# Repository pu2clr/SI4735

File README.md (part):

<meta name="google-site-verification" content="_wADvyP4vuP_aw0YTmu90mdAhz70vNwTF_pdAMMb0HY" />

# [PU2CLR SI4735 Library for Arduino](https://pu2clr.github.io/SI4735/)

[Se você estiver entendendo este texto, talvez queira ler este documento em Português](https://pu2clr.github.io/SI4735/extras/docbr/)

# Preface

|          |            |
|----------|------------|
|    | This document is aimed at the Arduino developers, radio experimenters, hobbyists and anyone interested in building a receiver based on the Si473X IC family from Silicon Labs. This project is about an Arduino library for the SI473X BROADCAST AM, SSB and FM/RDS RADIO RECEIVERS. Frequency ranges of AM and SSB modes are 150kHz to 30MHz, and FM mode is 64 to 108 MHz.

<BR>

This library is intended to provide an easy-to-use interface for controlling the SI47XX (including the boards ["PL102BA-S V:2.1 10628"](https://pu2clr.github.io/SI4735/extras/BOARD_PL102BA/) and ["NE928-10A V:01"](https://pu2clr.github.io/SI4735/extras/BOARD_NE928_10A_V_01/) based on SI4730) by using Arduino platform. [It also has support to the SSB mode on SI4735-D60 and SI4732-A10 devices](https://pu2clr.github.io/SI4735/#si4735-patch-support-for-single-side-band). __The communication protocol used by this library is the I²C__. 

This library was built based on ["AN332 Si47XX PROGRAMMING GUIDE REV 1.0"](https://web.engr.oregonstate.edu/~traylor/ece473/data_sheets/AN332.pdf) and __AN332 REV 0.8 UNIVERSAL PROGRAMMING GUIDE AMENDMENT FOR SI4735-D60/SI4732-A10 SSB AND NBFM PATCHES__. It also can be used on __all members of the SI473X family__ respecting, of course, the features available in each IC version. Please, follow the [contents below](https://pu2clr.github.io/SI4735/#contents) to get the most out of this document. 

This library can be freely distributed using the MIT Free Software model. 
By using or installing Library you are agreeing to the terms of the [MIT licence](https://pu2clr.github.io/SI4735/#mit-license).

[Copyright (c) 2019 Ricardo Lima Caratti](https://pu2clr.github.io/SI4735/#mit-license). 

Contact: __pu2clr@gmail.com__.

## Donate 

If you find this library useful and would like to support its continued development, you may optionally make a donation. Donations help cover the cost of components, modules, and laboratory testing used in the maintenance and improvement of this open-source project. Donations are entirely voluntary and do not grant any special product, service, warranty, support, or development priority. Please note that this project is maintained on a voluntary basis, and the author makes no commitment regarding schedules or deadlines for future releases, updates, or feature implementations. Click here to donate or use the QR code below. [Click here to donate](https://www.paypal.com/donate/?business=LLV4PHKTXC4JW&no_recurring=0&item_name=Consider+making+a+donation.+So%2C+I+can+purchase+components+and+modules+for+improvements+and+testing+of+this+library.&currency_code=USD) or use the QR code below.

## About Me

I hold a Master's degree in Educational Technology from the Federal University of Ceará, where I delved into the ways technology can enhance learning experiences. My passion for computer science led me to specialize in it, focusing on Distributed Systems Development with an Object-Oriented approach, at the University of Brasília. My academic journey began with a Bachelor's degree in Information Systems from the União Pioneira de Integração Social (UPIS-Brasília). Outside the classroom, my main hobbies are electronics and Amateur Radio. 

## Contents

1. [SI4735 Library construction history](https://pu2clr.github.io/SI4735/#si4735-library-construction-history)
2. [Thanks](https://pu2clr.github.io/SI4735/#thanks)
3. [Library Features](https://pu2clr.github.io/SI4735/#si4735-arduino-library-features)
4. [License Copyright](https://pu2clr.github.io/SI4735/#mit-license)
5. [Library Installation](https://pu2clr.github.io/SI4735/#library-installation)
6. [Command line arduino-cli and setup](https://github.com/pu2clr/SI4735/tree/master/examples#arduino-cli---a-faster-alternative-to-the-arduino-ide)
7. [Other Arduino Libraries Developed by the Author](https://pu2clr.github.io/SI4735/#other-arduino-libraries-developed-by-the-author)
8. [Groups and Forums](https://pu2clr.github.io/SI4735/#groups-and-forums)
9. [Your support is important](https://pu2clr.github.io/SI4735/#your-support-is-important)
11. [About the SI4732 and SI4735](https://pu2clr.github.io/SI4735/#about-the-si4732-and-si4735)
12. [Basic Schematic](https://pu2clr.github.io/SI4735/#schematic)
13. [Terminology](https://github.com/pu2clr/SI4735#terminology)
14. [Documentation](https://pu2clr.github.io/SI4735/#documentation)
   * [API Documentation](https://pu2clr.github.io/SI4735/extras/apidoc/html/) 
   * [About Class, Methods(functions) and custom data type structures](https://pu2clr.github.io/SI4735/#defined-data-types-and-structures)
   * [PU2CLR SI4735 Arduino Library methods (functions)](https://pu2clr.github.io/SI4735/extras/apidoc/html/)
   * [RDS support](https://pu2clr.github.io/SI4735/#rds)
   * [SSB support](https://pu2clr.github.io/SI4735/#si4735-patch-support-for-single-side-band)
   * [EEPROM support](https://pu2clr.github.io/SI4735/#eeprom-support)
   * [Digital Audio Support](https://pu2clr.github.io/SI4735/#digital-audio-support)
   * [Using an external active crystal or signal generator with SI47XX](extras/schematic#si473x-and-external-active-crystal-oscillator-or-signal-generator)
   * [Customizing PU2CLR Arduino Library](https://pu2clr.github.io/SI4735/#customizing-pu2clr-arduino-library)
15. [Hardware Requirements and Setup](https://pu2clr.github.io/SI4735/#hardware-requirements-and-setup)
16. [__SCHEMATIC__](https://pu2clr.github.io/SI4735/#schematic)
   * [All schematics](https://pu2clr.github.io/SI4735/extras/schematic)
   * [Component Parts](https://pu2clr.github.io/SI4735/#parts)
   * [Tips to build](https://pu2clr.github.io/SI4735/#tips-to-build)
   * [Other schematics](https://pu2clr.github.io/SI4735/extras/schematic)
     * [Atmega328 based board and OLED](extras/schematic#atmega328-based-board-and-oled)
     * [ESP32 based board](extras/schematic#esp32-based-board)
     * [Standalone ATmega328 with or without external Crystal (SI4735-D60 and LCD 16x2)](extras/schematic#standalone-atmega328-with-or-without-external-crystal-si4735-d60-and-lcd-16x2)
     * [Arduino / ATmega328 with Nokia 5110](extras/schematic#arduino--atmega328-with-nokia-5110)
     * [Basic schematic with TFT](extras/schematic#basic-schematic-with-tft)
     * [Arduino DUE/MEGA and touch TFT display](extras/schematic#arduino-duemega-and-touch-tft-display)
     * [Attiny85 basic circuit](extras/schematic#attiny85-basic-circuit)
     * [Bluepill - STM32F103C8 basic schematic](extras/schematic#bluepill---stm32f103c8-basic-schematic)
     * [Android and iOS Remote Control for PU2CLR Arduino Library DSP receivers](extras/schematic#android-and-ios-remote-control-for-pu2clr-arduino-library-dsp-receivers)
     * [External Mute Circuit](extras/schematic#external-mute-circuit)
     * [SI473X and external active crystal oscillator or signal generator](extras/schematic#si473x-and-external-active-crystal-oscillator-or-signal-generator)
     * [Band Pass Filter controlled by Arduino](extras/schematic#band-pass-filter-controlled-by-arduino)
     * [Storing data into the internal EEPROM before shutdowning](extras/schematic#storing-data-into-the-internal-eeprom-before-shutdowning)
17. [Most Frequent Problems](https://pu2clr.github.io/SI4735/#most-frequent-problems)
18. [Boards where this library has been successfully tested](https://pu2clr.github.io/SI4735/#boards-where-this-library-has-been-successfully-tested)
19. [Photos (Tools and Accessories)](https://pu2clr.github.io/SI4735/#photos-tools-and-accessories)
20. [References](https://pu2clr.github.io/SI4735/#references)
21. [Examples](https://pu2clr.github.io/SI4735/examples)
    * [Using Arduino Serial Monitor](examples/SI47XX_01_SERIAL_MONITOR) 
    * [LCD20x4, Encoder and buttons](examples/SI47XX_02_LCD_20x4_I2C)
    * [OLED, Encoder and button](examples/SI47XX_03_OLED_I2C)
    * [TFT and touch screen](examples/SI47XX_04_TFT)
    * [ATTINY85](examples/SI47XX_05_ATTINY85)
    * [ESP32](examples/SI47XX_06_ESP32)
    * [ESP8266](examples/SI47XX_06_ESP8266)
    * [STM32](examples/SI47XX_07_STM32) 
    * [FM RDS/RBDS](examples/SI47XX_10_RDS)
    * [About the board based on SI4730-D60 labeled "PL102BA-S V:2.1 10628"](https://pu2clr.github.io/SI4735/extras/BOARD_PL102BA/)
    * [About the board based on Si4730 labeled "NE928-10A V:01"](https://pu2clr.github.io/SI4735/extras/BOARD_NE928_10A_V_01/)
    * [Mobile Device as Remote Control to the SI4735 prototype](https://github.com/pu2clr/bluetooth_remote_control)
    * [Auto Band Pass Filter examples](examples/SI47XX_99_AUTO_BANDPASS_FILTER)
    * [Famous sketches and kits from third parties based on this Library](examples/SI47XX_KITS)
    * [Tools](https://github.com/pu2clr/SI4735/tree/master/examples/TOOLS)
22. [Third Party Projects](https://pu2clr.github.io/SI4735/extras/Third_Party_Projects)
23. [Videos](https://pu2clr.github.io/SI4735/#videos) 
    * [Project examples made by the author](https://pu2clr.github.io/SI4735/#project-examples-made-by-the-author)
    * [Third-party projects using this library](https://pu2clr.github.io/SI4735/#third-party-projects-using-this-library)
24. [Commercial Receivers based on Si47XX Family](https://pu2clr.github.io/SI4735/#commercial-receivers-based-on-si47xx-family) 

## Attention
* __The SI473X device can work from 1.6V to 3.6V. If you are not using a 3.3V Arduino board, that Arduino will send 5V signals to the SI473X device through the digital pins and the I2C bus. That configuration can make the system unstable or damage the Si473X device__. To fix this, use a logic shifter chip that converts between 3.3V and 5V logic.  
* __This library has been successfully tested on many boards including:  ESP32; STM32; Mega 2560;  DUE; ATmega328 and Atmega32u4 based boards; ATtiny85, Raspberry Pi Pico (RP2040) and more__. See [Boards where this library has been successfully tested](https://pu2clr.github.io/SI4735/#boards-where-this-library-has-been-successfully-tested).  
* __The Si47XX IC family  functionalities__ can be seen in the comparison matrix shown in table 1 (__Product Family Function__); pages 2 and 3 of the [“Si47XX PROGRAMMING GUIDE; AN332 (REV 1.0)”](https://web.engr.oregonstate.edu/~traylor/ece473/data_sheets/AN332.pdf).

## Why do skilled developers generally use libraries?

Technically, no Arduino application needs a library. In some cases, not using libraries may be the correct decision. But there are some good reasons to consider using a library.

Libraries typically allow for easier design and maintenance of code. A library may also implement the functionality you need on multiple hardware choices, thus making the code more portable.

Imagine that you want to use an LCD or other display device in a project that monitors temperature and atmospheric pressure conditions. There are several good libraries for display devices available for Arduino users, and most of the features you might want are implemented in these libraries. There is no point in re-inventing the wheel by avoiding a library. Unless you require a feature that no library supports, it is generally wise to use a library, especially since a library can make porting code to different hardware easier.

Use of a library can reduce programming complexity and boost application robustness. It makes life easier for other developers, and also for yourself. You do not have to be a software engineer to understand why this is the case. A library, in this way, is similar to an IC. It is often possible to manually implement the functionality of many IC chips in a circuit, but doing so would dramatically increase the cost, complexity, size, and sometimes the failure rate of a project. Circuits are often better when some functions are abstracted away inside an off-the-shelf IC chip. The user of an IC only needs to know how to interact with the chip, and not how the chip itself is wired.

Finally, if you already use a library to handle the I2C bus (Wire.h), TFT, OLED, SPI devices, and Serial UART communication, then it makes sense to use a library to handle the SI473X devices. The PU2CLR Arduino Library can offer more comfort, development agility, and robustness to your project. Unlike closed-source solutions, this library is open-source. This means you can learn how the library works by studying the code, if you choose.

## SI4735 Library construction history

I began my journey to create an Arduino library for the SI473X family of devices in early November 2019. The initial plan was to construct a receiver using an Arduino board, a handful of components, and the SI4735 device manufactured by Silicon Labs. After watching some videos on YouTube, it became clear that a receiver based on the SI4735-D60 had the potential to exceed the original scope of the project—__it could even receive amateur radio and citizens band stations in SSB mode__. Through forums and websites, I discovered a significant demand from hobbyists and experimenters interested in using the SI4735 device, particularly for SSB mode. With this in mind, I shifted my focus. Instead of merely developing a basic receiver around the SI4735, __I opted to create a comprehensive Arduino library that would fully support not only the SI4735 but the entire SI473X device family__.

With this library, more than 60 examples were developed using various display types. [These examples can assist the experimenter in building their own receiver](https://github.com/pu2clr/SI4735/tree/master/examples).

Judging by the groups created around the SI47XX devices, I estimate that this library is currently being used by thousands of experimenters, applications and commercial receivers. If you are an experimenter or a radio enthusiast and want to try to build your own receiver based on the SI473X devices, then this library is for you.  

The following video is a little joke that shows the trajectory of the construction of this library. [__"PU2CLR SI4735 Arduino Library. IT IS OPEN SOURCE IT IS FREE. IT IS FOR YOU"__](https://www.youtube.com/embed/aB02Qry5-bU).

{% include libhistory.html %}

<BR> 

## Thanks

* Mrs. [Nancy Daniels Yoga](https://github.com/LadyRoninEngineer/Si473x), for sharing experiences and suggestions for noise reduction on the I2C bus and also for sharing the excellent board projects for the SI4732-A10 device
* Mr. Tom Nardi, for his great article ["Multi-Band Receiver On A Chip Controlled By Arduino"](https://hackaday.com/2020/03/02/multi-band-receiver-on-a-chip-controlled-by-arduino/) on Hackaday website
* Mr. Gert Baak, [PE0MGB](https://www.qrz.com/db/PE0MGB), for library improvements suggestions and the Article [Arduino All band radio with SI4735 by Gert PE0MGB](https://www.pi4raz.nl/razzies/razzies202009.pdf)
* Dr. George R Steber, [WB9LVI](https://www.qrz.com/db/WB9LVI) for his great article __NanoSSB RX - An Ultra Low Cost SSB Multiband Receiver__ on __ARRL QEX Magazine__ (November/December 2021)
* Mr. Benjamin Neveu, for his article __SSB Receiver Controlled by a Smartphone__ publised on __ARRL QEX Magazine__(September/October 2022)
* Mr. Jim Reagan, [W0CHL](https://www.qrz.com/db/W0CHL), for contributions on circuit design and user interface
* [Mr. Vadim Afonkin](https://youtu.be/fgjPGnTAVgM), for making available the SSBRX patches for SI4735-D60 on his [Dropbox repository](https://www.dropbox.com/sh/xzofrl8rfaaqh59/AAA5au2_CVdi50NBtt0IivyIa?dl=0)
* Mr. Luiz Carlos, [PT2MC](https://www.qrz.com/db/PT2MC), for guidance on external mute circuits
* Mr. Thiago Lima, for sharing his board project based on the ESP32 and SI4732-A10 devices
* Mr. Francisco Scaramella, for the suggestions and contributions provided in the electronics field as well as for the testing of the functions implemented in this library
* Mr. David Kellmer (USA), for suggesting corrections on the documentation and sketches 
* WH2Q, Morikaku Gotoh, for his suggestion about Automatic Volume Control on AM mode
* Mr. Diego Stanfield, for testing the SI4732-A10 with SSB
* All members of the Facebook groups ["Si47XX for radio experimenters"](https://www.facebook.com/groups/532613604253401/) and ["Si47XX para radioescutas"](https://www.facebook.com/groups/1121785218031286/) for the suggestions and corrections during the development of this project.
* Mr. Toni, for his post [SI4735 SI4732 all band radio receiver LW MW FM SW](https://xtronic.org/circuit/audio/si4735-si4732-all-band-radio-receiver-mw-fm-sw/)
* Mr. Scacchi Ugo, for the post [HAM RADIO  -  ARDUINO SI4735 Based Radio](https://www.i2sdd.net/ARDUINO/SI4735/si4735.HTML)
* Mr. Miguel Angelo Bartié, PY2OHH, for the post [RECEIVER FM/MW/SW(AM SSB and CW) with SI4735 prototype](https://www.qsl.net/py2ohh/trx/si4735/SI4735.html)   
* Mr. Felix Angga, for his great receiver based on SI4735 interface - [SlametRadio](https://github.com/felangga/slametradio) 
* Mr. DAVID W ZANTOW, [N9EWO](https://www.qrz.com/db/N9EWO), for his Reviews about [ATS-25 / ATS25 / LW / MW / SW / FM DSP Receiver](https://www.qsl.net/n9ewo/ats25.html)
* Mr. Dalton Herrewynen for documentation corrections and improvements.

<BR>

## Your support is important.

If you want to support this library development, consider joining this project via Github. Alternatively, make suggestions on new features and report errors if you find them. Thank you!

[Go to contents](https://pu2clr.github.io/SI4735/#contents)

## SI4735 Arduino Library Features

This library uses the I²C communication protocol and implements most of the functions offered by Si47XX (BROADCAST AM / FM / SW / LW RADIO RECEIVER) IC family from Silicon Labs. This library also has primitive functions that make it easier for you to implement commands that may not have been implemented yet. See [setProperty, getProperty sendCommand, getCommandResponse and getStatusResponse](https://pu2clr.github.io/SI4735/extras/apidoc/html/group__group10.html) functions and also [How to customize PU2CLR Arduino Library](https://pu2clr.github.io/SI4735/#customizing-pu2clr-arduino-library). It is worth noting, however, that this library is constantly improving. Check the API documentation before implementing a new function. It is likely that your function is already implemented. [See the API documentation for this library](https://pu2clr.github.io/SI4735/extras/apidoc/html/). __The main features of this library are listed below__.

1. Open Source. It is free. You can use, copy, modify, merge, publish, distribute, sublicense, and/or sell copies of the Software. See [MIT License](https://pu2clr.github.io/SI4735/#mit-license) to know more.   
2. Built based on [AN332 SI47XX PROGRAMMING GUIDE (REV 1.0)](https://web.engr.oregonstate.edu/~traylor/ece473/data_sheets/AN332.pdf) and __AN332 REV 0.8 UNIVERSAL PROGRAMMING GUIDE AMENDMENT FOR SI4735-D60 SSB AND NBFM PATCHES__
3. C++ Language and Object-oriented programming. You can easily extend the SI4735 class by adding more functionalities. See [Customizing PU2CLR Arduino Library](https://pu2clr.github.io/SI4735/#customizing-pu2clr-arduino-library)
4. Available on Arduino IDE (via Manage Libraries). Easy to install and use. See [Library Installation](https://pu2clr.github.io/SI4735/#library-installation)
5. Cross-platform. You can compile and run this library on most of boards supported by the Arduino IDE (Examples: ATtiny85, boards based on ATmega328 and ATmega-32u4, ATmega2560, ARM Cortex, STM32, Arduino DUE, ESP32 and more). See [Boards where this library has been successfully tested](https://pu2clr.github.io/SI4735/#boards-where-this-library-has-been-successfully-tested)
6. Simplifies projects based on SI4735
7. __I²C communication protocol__ and Automatic I²C bus address detection
8. [More than __120__ functions implemented](https://pu2clr.github.io/SI4735/extras/apidoc/html/). You can customize almost every feature available on Si47XX family
9. [More than 60 examples to guide the user](https://github.com/pu2clr/SI4735/tree/master/examples)
10. [RDS support](https://pu2clr.github.io/SI4735/#rds)
11. [SSB (Single Side Band) patch support](https://pu2clr.github.io/SI4735/#si4735-patch-support-for-single-side-band)
12. Clock reference selection (crystal or external clock reference)
13. FM Receive de-emphasis to 50 or 75 μs selection, AGC, AVC and filter controls, and more... 

[Go to contents](https://pu2clr.github.io/SI4735/#contents)

<BR>

## Groups and Forums 

There is a __Facebook__ group called [__Si47XX for Radio Experimenters__](https://www.facebook.com/groups/532613604253401/) where the purpose is exchanging experiences with projects based on Silicon Labs  SI47XX IC family. You will be welcome to the group [Si47XX for Radio Experimenters](https://www.facebook.com/groups/532613604253401/).

You can also be a member of __group.io__ [SI47XX for hobbyists](https://groups.io/g/si47xx)

{% include groupio.html %}

[Follow a project using this library on hackaday.io](https://hackaday.io/project/170145-si4735-ssb-receiver-controlled-by-arduino)

## MIT License 

Copyright (c) 2019 Ricardo Lima Caratti

Permission is hereby granted, free of charge, to any person obtaining a copy
of this software and associated documentation files (the "Software"), to deal
in the Software without restriction, including without limitation the rights
to use, copy, modify, merge, publish, distribute, sublicense, and/or sell
copies of the Software, and to permit persons to whom the Software is
furnished to do so, subject to the following conditions:

The above copyright notice and this permission notice shall be included in all
copies or substantial portions of the Software.

THE SOFTWARE IS PROVIDED "AS IS", WITHOUT WARRANTY OF ANY KIND, EXPRESS OR
IMPLIED, INCLUDING BUT NOT LIMITED TO THE WARRANTIES OF MERCHANTABILITY,
FITNESS FOR A PARTICULAR PURPOSE AND NONINFRINGEMENT. IN NO EVENT SHALL THE
AUTHORS OR COPYRIGHT HOLDERS BE LIABLE FOR ANY CLAIM, DAMAGES OR OTHER
LIABILITY, WHETHER IN AN ACTION OF CONTRACT, TORT OR OTHERWISE, ARISING FROM,
OUT OF OR IN CONNECTION WITH THE SOFTWARE OR THE USE OR OTHER DEALINGS IN THE
SOFTWARE.

<BR>

[Go to contents](https://pu2clr.github.io/SI4735/#contents)

<BR>

## Library Installation

You can install this library on your Arduino environment using different methods. The best ways to do that are described below.  

### Installing via Arduino IDE

This is the easiest method to install this library.

#### The image below shows the Arduino IDE Manage Libraries interface.

#### The image below shows the PU2CLR Si4735 Library finding process.

<BR>

<BR>

#### The video below shows how to install the PU2CLR Arduino Library on your Arduino IDE. 

{% include libinstalling.html %}

### Installing via this repository 

<BR>

First, you have to [download](https://github.com/pu2clr/SI4735/archive/master.zip) this library in zip format. 
After, unzip the SI4735-master.zip file in your Arduino Library folder. 

* On __Windows__: "My Documents\Arduino\libraries"
* On __MAC OS__: ˜/Documents/Arduino/libraries
* On __Linux__: ˜/Documents/Arduino/libraries

With that approach, you will have the __most current version__ of the library. However, __it may not be the most stable version__. This is because the current version is always in development. [Prefer releases](https://github.com/pu2clr/SI4735/releases).
Do you need some old version (release) of this library?  If so, [check here](https://github.com/pu2clr/SI4735/releases). 

## Installing the most current version via arduino-cli

The commands below Install the latest version of the PU2CLR SI4735 Arduino Library from github. 
As said before, unlike a release (installed from Arduino IDE) this method installs the current version of the PU2CLR SI4535 Arduino Library (latest modifications even if not yet released).

### On macOS or Linux

```bash
curl -fsSL https://raw.githubusercontent.com/arduino/arduino-cli/master/install.sh | sh
export ARDUINO_LIBRARY_ENABLE_UNSAFE_INSTALL=true
./bin/arduino-cli lib install --git-url https://github.com/pu2clr/SI4735
```

### On Windows 10 or 11

Run the command shell (cmd / Command Prompt) and follow the steps below.

```bash
echo off  
curl -fsSL https://downloads.arduino.cc/arduino-cli/arduino-cli_latest_Windows_64bit.zip --output arduinocli.zip
tar -xf arduinocli.zip 
set ARDUINO_LIBRARY_ENABLE_UNSAFE_INSTALL=true
.\arduino-cli lib install --git-url https://github.com/pu2clr/SI4735
```

### About library installation and programming setup see also:

* More about arduino-cli click [here](https://github.com/pu2clr/SI4735/tree/master/examples#arduino-cli---a-faster-alternative-to-the-arduino-ide).
* About Arduino IDE, arduino-cli, SI4735 Arduino Library examples and programming setup, see the scripts below 
  * On macOS or Linux 
    * examples/__lib_si4735_basic_install.sh__ - Installs arduino-cli and some libraries and boards used by some the examples
    * examples/__install_all_libraries_and_boards.sh__ - Installs all libraries and all boards used by the examples
    * examples/__compile_all.sh__ - compiles all examples and save the binaries in your Downloads folder
  * On Windows 10 or 11 
    * examples/__lib_si4735_basic_install.bat__ - Installs arduino-cli and some libraries and boards used by some the examples
    * examples/__install_all_libraries_and_boards.bat__ - Installs all libraries and all boards used by the examples
    * examples/__compile_all.bat__ - compiles all examples and save the binaries in your Downloads folder

## Bords setup on your Arduino IDE

It will be useful if you intend to use ESP32, ESP8266, Teensy, Raspbery PI PICO, Arduino DUE, ATTiny etc. 

On Arduino IDE, preferences, Aditional boards manager URls. See image below.

The list below refers to the board URLs used by the examples. You can remove the boards you do not want to use.

```bash
http://arduino.esp8266.com/stable/package_esp8266com_index.json 
http://dan.drown.org/stm32duino/package_STM32duino_index.json 
http://drazzy.com/package_drazzy.com_index.json 
https://files.seeedstudio.com/arduino/package_seeeduino_boards_index.json 
https://github.com/earlephilhower/arduino-pico/releases/download/global/package_rp2040_index.json 
https://github.com/stm32duino/BoardManagerFiles/raw/main/package_stmicroelectronics_index.json 
https://github.com/stm32duino/BoardManagerFiles/raw/master/STM32/package_stm_index.json 
https://mcudude.github.io/MegaCore/package_MCUdude_MegaCore_index.json 
https://mcudude.github.io/MightyCore/package_MCUdude_MightyCore_index.json 
https://mcudude.github.io/MiniCore/package_MCUdude_MiniCore_index.json 
https://raw.githubusercontent.com/DavidGuo-CS/OSOYOO_Arduino/main/package_osoyoo_boards_index.json 
https://raw.githubusercontent.com/VSChina/azureiotdevkit_tools/master/package_azureboard_index.json 
https://raw.githubusercontent.com/damellis/attiny/ide-1.6.x-boards-manager/package_damellis_attiny_index.json 
https://raw.githubusercontent.com/dbuezas/lgt8fx/master/package_lgt8fx_index.json 
https://raw.githubusercontent.com/espressif/arduino-esp32/gh-pages/package_esp32_index.json 
https://raw.githubusercontent.com/nulllaborg/arduino_nulllab/master/package_nulllab_boards_index.json 
https://www.pjrc.com/teensy/package_teensy_index.json
``` 

After adding the Board URL you want to use, go to Tools menu, select the Boards item and then select Boards Manager... option. Finally,  look for your board and install it.

[See the ESP32 setup example on Arduino IDE](https://github.com/pu2clr/SI4735/tree/master/examples/SI47XX_06_ESP32) 

[Go to contents](https://pu2clr.github.io/SI4735/#contents)

<BR>

## About the SI4732 and SI4735  

The SI4732-A10 and SI4735-D60 are DSP receivers IC from Silcon Labs. They have great performance on AM, SSB (LW/MW/SW) from 150kHz to 30MHz and FM (VHF) from 64 to 108 MHz. __It is important to note that the engineers and programmers at Silicon Labs did an excellent job by implementing all the internal resources in this IC family. This library implements just the interface that allows you to use the SI473X resources with Arduino based board controller__. 
The SI473X can be programmed by sending commands and getting responses. You can control it via a microcontroller like Arduino using I²C communication protocol. To make the SI473X perform an action, the microcontroller has to send a set of bytes (command and arguments) that the device interprets and executes the given command. The image below illustrates the interaction between the MCU and the SI473X device. 

<BR>

### Interaction between Arduino based board and SI473X devices via  I²C  interface

<BR>

### Functional Block Diagram

The image below shows the SI473X-D60 block diagram. It was extracted from Silicon Labs Si4730/31/34/35-D60 / BROADCAST AM/FM/SW/LW RADIO RECEIVER (page 21). __Note that the author of this Library highlights in red the pin operating voltages that can be connected to the Arduino__. Be aware of the operating voltage of the Arduino pins you will use in your project. Preferably use an Arduino with 3.3V operating voltage. If you are not using a 3.3V version of Arduino, you must use a kind of 5V to 3.3V converter on RST, SCLK, SDIO and SEN (depending on your project). 

According to the Si47XX PROGRAMMING GUIDE/AN332, the Si4732-A10 has the same firmware FMRX component and AM_SW_LW RX component as that of Si4735-D60. It is considered as the most recent revision as D60. So, __all descriptions related to the SI4735-D60 also apply to Si4732-A10__. __Including SSB patch support__. See the Si4732-A10 block diagram below.  

#### SI4735-D60 and SI4732-A10 I²C bus address 

While the Si4735-D60 provides the 0x11 I²C bus address when the SEN pin is connected to the ground, the SI4732-A10 provides the same address when the SEN pin is connected to the +VCC.  Also, this library provides the function __getDeviceI2CAddress__ to detect the I²C bus address automatically. This way, you don't need to worry about this setup if you use this function. See [getDeviceI2CAddress()](https://pu2clr.github.io/SI4735/extras/apidoc/html/group__group05.html#ga668008457910e916ebadf15bda2e5b29).

## Hardware Requirements and Setup

This library has been written for the Arduino platform and has been successfully tested on many boards. See [Boards where this library has been successfully tested](https://pu2clr.github.io/SI4735/#boards-where-this-library-has-been-successfully-tested)

### Arduino 5V and Si4735

* __THE SI4735 IS A 3.3V PART. IF YOU ARE NOT USING A 3.3V VERSION OF ARDUINO or anothe board, YOU HAVE TO USE A KIND OF 5V-3.3V BIDIRECTIONAL CONVERTER. Also pay attention to the appropriated pinout of your board to select the correct interrupt (IRQ- if you are using), RST, SDIO and SCLK pins. The table below shows some Arduino board pinout.__ 

<BR>

|Board | InterrupT (IRQ) Pins| I²C / TWI pins | successfully tested | Voltage converter |
|------|---------------------| ---------------| ------------------- | ----------------- | 
| 328-based <br> (Nano, Uno or Mini 5V) |	D2 and D3 | A4 (SDA/SDIO), A5 (SCL/SCLK) |  Yes | Yes | 
| 328-based <br> (Pro Mini 3.3 / 8Mhz) | D2 and D3 | A4 (SDA/SDIO), A5 (SCL/SCLK) |  Yes | No | 
| LTG8F328 <br> based board | D2 and D3 | A4 (SDA) and A5 (SCL) | Yes | No | 
| Mega 2560 | 2, 3, 18, 19, 20 and  21 | 20 (SDA/SDIO), 21 (SCL/SCLK) | Yes | Yes |
| 32u4-based <br> (Micro, Leonardo or Yum)	| 0, 1, 2, 3 and 7 | 2 (SDA/SDIO), 3 (SCL/SCLK) |  Yes | Yes |
| Zero | Any digital pins except pin 4 | D8 (SDA/SDIO) and D9 (SCL/SCLK)  | Not tested | No |
| Due	| Any digital pins | 20 (SDA/SDIO), 21 (SCL/SCLK) | Yes  |  No |
| ESPRESSIF ESP32 | Any GPIO pins |  Most pins (usually 21 and 22) | Yes | No | 
| ESPRESSIF ESP8366 | GPIO13 and GPIO14 | GPIO4 (SDA) and GPIO5 (SCL) | Yes | No | 
| STM32F103  | PA0, PA1 | PB6 (SCL) and PB7 (SDA) | Yes | No |
| STM32F104  | PA0, PA1 | PB6 (SCL) and PB7 (SDA) | Yes | No |
| RP2050 <br> Rpi Pico| Any GPIO pins | GP1 (SCL) and GP0 (SDA) | Yes | No |  

### Schematic

The main purpose of the schematic below (prototype) is to test the Si4735 Arduino Library. It does not intend to be a real radio for exigent listeners. However, it is possible to start with it and then, if you wish, you can include some devices to the circuit to improve, for example, its sensibility beyond other desired features.
[Click here to see a complete set of schematics and tips](https://pu2clr.github.io/SI4735/extras/schematic)

The image below shows a version of Silicon Labs SSOP Typical Application Schematic connect to the host MCU (Arduino Pro Mini 3.3V). __Pay attention to the Si4735-D60 SEN pin (16). When the SEN pin is connected to the ground, the I²C bus address is 0x11. When the SEN pin is connected to +3.3V, the I²C bus address is 0x63. By default, the "Si4735 Arduino Library" uses the 0x11 I²C bus address (SEN pin connected to GND). If you want to use the address 0x63 (SEN connected on +3.3V), see the functions (methods) getDeviceI2CAddress, setDeviceI2CAddress and setDeviceOtherI2CAddress__.   

<BR>

#### Basic Schematic with SI4735-D60

#### Basic Schematic with SI4732-A10

__Please, check the folder [extras/schematic/](https://pu2clr.github.io/SI4735/extras/schematic)__. There, you will find other schematics with OLED, LCD, Nokia 5110, TFT, buttons and encoders setup. Also, check the comments at the beginning of each sketch example. You will find the SI473X, button, encoder, display and Arduino settings. 

#### The picture below shows the SI4735-D60/SI4730-D60 pinout (SSOP)

#### The picture below shows the SI4732-A10 pinout (16L SOIC Package)

#### The picture below shows the SI473X pinout (QFN)

* The SI4735-D60 and SI4732-A10 have SSB patch support
* __See some Shortwave antenna configuration on__  [Si47XX ANTENNA, SCHEMATIC, LAYOUT, AND DESIGN GUIDELINES; AN383](https://www.silabs.com/documents/public/application-notes/AN383.pdf)

* __Pay attention to the appropriated Arduino pinout to select the correct interrupt (IRQ), RST, SDIO and SCLK pins. The previous table shows some Arduino board pinout__.  
* __Be sure about the pinout of your device and Arduino connections. For example: the Si4735-D60/Si4730_D60 SEN pin (16 on SSOP version and 6 on QFN version) when connected to the ground, the I²C bus address is 0x11. When this pin is connected to +3.3V, the I²C bus address is 0x63__. See the functions [getDeviceI2CAddress](https://pu2clr.github.io/SI4735/#getdevicei2caddress) and [setDeviceI2CAddress](https://pu2clr.github.io/SI4735/#setdevicei2caddress) to correct setup. If you follow the schematic used in this project, you do not need to do anything (the default I²C bus address is 0x11). If you do not know how this pin is configured on the board, use [getDeviceI2CAddress](https://pu2clr.github.io/SI4735/#getdevicei2caddress).  

<BR>

#### The image bellow shows the Silicon Labs SSOP Typical Application Schematic.

<BR>

### Parts

The table below shows the component parts used to build the radio prototype based on Si4735 and used the Silicon Labs SSOP Typical Application Schematic as main source. However, some parts were included by the author of this project. 

|Part	| Description |
|-------| ------------ |
| C1    | 22nF Monolithic Multilayer Chip Ceramic non polarized capacitor (Place it close to VA pin)|
| C2    | 1nF Monolithic Multilayer Chip Ceramic non polarized capacitor |
| C3    | 470nF Monolithic Multilayer Chip Ceramic non polarized capacitor| 
| C4    | 100nF Monolithic Multilayer Chip Ceramic non polarized capacitor (Place it close to VD pin)|
| C5 and C6 | 22pF (Crystal load capacitors) | 
| C7 and C8 *1 | 4.7uF Monolithic Multilayer Chip Ceramic non polarized capacitor | 
| R3    | 2.2K |
| (R4 and R5) *2 | 2.2K to 10K (pull-up resistors) |
| L1 | Ferrite loop stick (about 500 μH) |
| X1    | 32.768 kHz crystal |
| SI4735 | digital CMOS AM(LW, MW and SW)/FM radio receiver IC |

  * *1: C7 and C8 are ceramic capacitors included by the author of this project. They are not present on the original Silicon Labs schematic. Actually, you can use also electrolytic capacitors. Values between 2.2uF to 10uF will work well. 
  * *2: R4 and R5 are pull-up resistor included by the author of this project. They are not present on the original Silicon Labs schematic. This will also depend on other devices connected to the same I²C bus.  __Always try to use the lowest possible value__.

__Notes from Silicon Labs Broadcast AM/FM/SW/LW Radio Receiver documentation (page 12)__:
* Place C1 close to VA and C4 close to VD pin.
* All grounds connect directly to GND plane on PCB.
* Pins 6 and 7 are not connects, leave floating.
* Pins 10 and 11 are unused. Tie these pins to GND.
* To ensure proper operation and receiver performance, follow the guidelines in “AN383: Si47xx Antenna, Schematic,
* Layout, and Design Guidelines.” Silicon Laboratories will evaluate schematics and layouts for qualified customers.
* Pin 8 connects to the FM antenna interface, and pin 12 connects to the AM antenna interface.
* Place Si473x-D60 as close as possible to the antenna and keep the FMI and AMI traces as short as possible.

[Go to contents](https://pu2clr.github.io/SI4735/#contents)

<BR>

### The main Si4735-D60 and Si4732-A10 features

* FM (VHF) support (64–108 MHz)
* AM (MW) band support (520–1710 kHz)
* SW band support (2.3–26.1 MHz)
* LW band support (153–279 kHz)
* Allows firmware upgrade. Including the possibility of adjustments to demodulate SSB.
* Advanced AM/FM seek tuning
* Automatic frequency control (AFC)
* Automatic gain control (AGC)
* Digital FM stereo decoder
* AM/FM/SW/LW digital tuning
* SSB patch support
* RDS/RBDS processor
* Digital audio out (__Attention__: Crystal and digital audio mode cannot be used at the same time)
* I²C and SPI interface 
* Great Programming Guide and additional documentation to deal with the device

[Go to contents](https://pu2clr.github.io/SI4735/#contents)

<BR>

## Terminology

| Term | Description |
| ---- | ----- |
| API  | Application Programming Interface (API). In this context, it is an interface that you can use to simplify the implementation and maintenance of your software (Arduino sketch). All API documentation about this library can be found on [https://pu2clr.github.io/SI4735/extras/apidoc/html/index.html](https://pu2clr.github.io/SI4735/extras/apidoc/html/index.html). | 
| Arduino Libraries|Libraries are files written in C or C++ (.c, .cpp) which provide your sketches with extra functionality. The SI4735 Library provides extra functionalities to make easier the Arduino deal with Si473X devices| 
| BPF  | Band Pass Filter |
| DFS  | I²S - digital frame synchronization input |
| DIN  | I²S - digital data input |
| DCLK | I²S - digital bit synchronization input clock |
| ESD  | Electrostatic discharge. Device used to protect the receiver from static electricity discharge |
| IDE  | Integrated Development Environment|    
| I²C  | [I²C - Inter-Integrated Circuit](https://pt.wikipedia.org/wiki/I²C)|  
| I²S  | Serial bus interface used for connecting digital audio devices 
| Sketch |Name that Arduino environment uses for a program|
| Interrupt |In this context, it is an Arduino Resource. Allows important tasks to be performed regardless of the flow of your program|
| C++ | A object-oriented programming (OOP) language. It is a superset of the C language with an additional concept of "classes." |
| programming guide | In this context it refers to [Si47XX PROGRAMMING GUIDE (REV 1.0)](https://web.engr.oregonstate.edu/~traylor/ece473/data_sheets/AN332.pdf)|
| LNA | Low Noise Amplifier |
| POC | Proof of Concept|
| SEN | Serial enable pin, active low, used as device select in 3-wire and SPI operation and address selection in 2-wire operation| 
| CTS | Clear to send |
| STC | Seek/Tune Complete |
| RESP | Response byte (n = 1 to 15) |
| RESPONSEn | Response register (16-bit) in 3-Wire mode (n = 1 to 8)| 
| RST  | Also RSTb—Reset pin, active low |
| RCLK | External reference clock |
| SSB | [Single Side Band](https://en.wikipedia.org/wiki/Single-sideband_modulation) | 
| Attack | attack-time delay -  the time needed for a receiver to respond to an incoming signal |
| SDIO | Serial data in/data out pin|
| SCLK | Serial clock pin |
| Soft Mute | Resource used to attenuate the audio outputs and minimize audible noise in very weak signal conditions | 
| Firmware Upgrades | The Si4732-A10 and SI4735-D60 contain on-chip program  RAM to accommodate minor changes to the firmware | 

[Go to contents](https://pu2clr.github.io/SI4735/#contents)

<BR>

## Documentation 

{% include apidoc.html %}

This library has two documentation sources: 

* [SI4735 Arduino Library documentation generated by Doxygen (updated)](https://pu2clr.github.io/SI4735/extras/apidoc/html/)
* [Legacy documentation (not updated frequently)](https://github.com/pu2clr/SI4735/wiki) 

[Doxygen](http://www.doxygen.nl/index.html) is a tools that can generate documentation from source code. This tools help the development team to keep the documentation updated. 

If you prefer, you can also read the documentation directly from the [SI4735.cpp](https://pu2clr.github.io/SI4735/SI4735.cpp) and [SI4735.h](https://pu2clr.github.io/SI4735/SI4735.h). These files are also well documented. 

### Main functions 

This library has more than 120 functions. The table below shows the mains functions used in a regular receiver. Full details on the functions shown below can be read on [https://pu2clr.github.io/SI4735/extras/apidoc/html/](https://pu2clr.github.io/SI4735/extras/apidoc/html/).

| Method / Function               | Description |
| ------------------                | ----------- | 
| setup                             | Use this function to start the device up with the parameters shown below. |
| getStatus                         | Used to get the current status of the Si4735. |
| getCurrentRSSI                    | Get the current receive signal strength (0–127 dBμV). |
| getCurrentSNR                     | Gets the current SNR metric (0–127 dB). |
| getFrequency                      | Gets the current frequency of the Si4735. |
| frequencyUp                       | Increments the current frequency on current band/function by using the current step. |
| frequencyDown                     | Decrements the current frequency on current band/function by using the current step. |
| setFrequencyStep                  | Sets the current step value. |
| setVolume                         | Sets volume level (0 to 63). |
| setFM                             | Sets the radio to FM function. |
| isCurrentTuneFM                   | Returns true if the current function is FM (FM_TUNE_FREQ). |  
| getCurrentPilot                   | Checks the current pilot. Indicates stereo pilot presence. | 
| setAM                             | Sets the radio to AM function. It means: LW MW and SW. |
| setAmSoftMuteMaxAttenuation       | Sets the Am Soft Mute Max Attenuation. |
| setAutomaticGainControl           | Automatic Gain Control setup. |
| getAutomaticGainControl           | Queries Automatic Gain Control STATUS. |
| setBandwidth                      | Selects the bandwidth of the channel filter for AM reception. |
| isAgcEnabled                      | Checks if the AGC is enabled (returns true if enabled). |
| setRdsConfig                      | Sets RDS property. |
| getRdsStatus                      | Gets the RDS status. Store the status in currentRdsStatus member. COMMAND FM_RDS_STATUS. |
| getRdsReceived                    | Get the Rds Received FIFO. |
| getRdsSync                        | Get the Rds Sync. Returns true if RDS currently synchronized. |
| getRdsSyncFound                   | Get the Rds Sync Found. Returns true if found RDS synchronization. |
| getRdsText2A                      | Gets the Text processed for the 2A group. |
| getRdsText2B                      | Gets the Text processed for the 2B group. |
| getRdsText0A                      | Gets the station name and other messages. |
| getRdsTime                        | Gets the RDS time and date when the Group type is 4. | 
| reset                             | Reset the SI473X.  |
| queryLibraryId                    | Queries the library information of the Si47XX device. | 
| patchPowerUp                      | This method can be used to prepare the device to apply SSBRX patch. |
| downloadPatch                     | Transfers the content of a SSB patch stored in an array of bytes to the SI4735 device. |
| downloadPatchFromEeprom           | Transfers the content of a SSB patch stored in an eeprom to the SI4735 device. |
| setSSBConfig                      | Sets the SSB receiver mode. |
| setSSB                            | Tunes the SSB (LSB or USB) receiver to a frequency between 520 and 30 MHz in 1 kHz steps.|
| setSSBAutomaticVolumeControl      | Sets SSB Automatic Volume Control (AVC) for SSB mode. |
| setSSBBfo                         | Sets the SSB Beat Frequency Offset (BFO). |
| setSSBAudioBandwidth              | SSB Audio Bandwidth for SSB mode. |
| setSBBSidebandCutoffFilter        | Sets SBB Sideband Cutoff Filter for band pass and low pass filters. |
| setTuneFrequencyAntennaCapacitor  | Only FM. Freeze Metrics During Alternate Frequency Jump. |
| setI2CFastModeCustom              | Sets the I²C bus to a given value. |
| setI2CStandardMode                | Sets I²C bus to 100kHz. |
| setAudioMuteMcuPin                | This function sets the mcu digital pin you want to use to control the external audio mute circuit. | 

[Go to contents](https://pu2clr.github.io/SI4735/#contents)

### Defined Data Types and Structures

The Si47XX family works with many internal data that can be represented by data structure or defined data type in C/C++. These C/C++ resources have been used widely here. This approach made the library easier to build and maintain. Each data structure created here has its reference (name of the document and page on which it was based). In other words, to make the SI47XX device easier to deal with, some defined data types were created to handle  byte and bits to process commands, properties and responses. __The goal of this approach is separating data from code__. 

All data types defined in Si4735 Arduino Library are explained [here](https://pu2clr.github.io/SI4735/extras/apidoc/html/)

### Public methods 

This library was developed using the C++ language and the Object-oriented Programming approach. Methods are functions that belong to the class, in this case SI4735 class. Click [here](https://pu2clr.github.io/SI4735/extras/apidoc/html/group__group01.html) to go to API docummentation.

All methods defined in Si4735 class are explained [here](https://pu2clr.github.io/SI4735/extras/apidoc/html/). The list below refers to the method groups implemented by the Si4735 class.   

#### Si47XX device setup and startup

Methods of this group are useful to configure the way that the Si47XX devices have to be initiate. 

#### Firmware Information

Allows to query the part number, chip revision, firmware revision, patch revision and component revision numbers.

#### Current Status 

The Si4735 class has a set of methods to query the current frequency, RSSI, SNR, multipath, and the antenna tuning capacitance value (0-191).

#### Current AGC Status

Methods to query AGC status.  Returns whether the AGC is enabled or disabled and it returns the gain index. 

#### Si4735 filters configuration

The SI4735 class has a set of methods to setup filters on AM and SSB mode.

#### Audio 

Methods to setup the audio mode (Digital or Analog), volume, mute etc. 

### RDS

This library implements some RDS features of the SI4735. All functions to deal with RDS are documented [here](https://pu2clr.github.io/SI4735/extras/apidoc/html/group__group16.html). Below you have some videos showing the RDS functionalities implemented by the PU2CLR Si4735 Arduino Library.

{% include videoRDS2.html %}

{% include videoRDS1.html %} 

See [RDS example implementations for more details](https://github.com/pu2clr/SI4735/tree/master/examples/SI47XX_10_RDS).

The list below points to some sketch examples that use RDS implementation. 

* [ATS-20 and 20+](https://github.com/pu2clr/SI4735/tree/master/examples/SI47XX_KITS/AliExpress/SI473X_ALL_IN_ONE_OLED_RDS_CHINESE_V8r) 
* [All band receiver with Nokia Display and RDS](https://github.com/pu2clr/SI4735/tree/master/examples/SI47XX_09_NOKIA_5110/ALL_IN_ONE_ENCODER_RDS) 
* [All Band receiver with Arduino DUE or Arduino Mega2560, TFT Touch and RDS](https://github.com/pu2clr/SI4735/tree/master/examples/SI47XX_16_ARDUINO_DUE_MEGA/SI47XX_02_RDS_TFT_TOUCH_SHIELD_35_V2)
* [TFT and Touch examples with RDS support](https://github.com/pu2clr/SI4735/tree/master/examples/SI47XX_10_RDS)

__ATTENTION:__ 
While utilizing interrupts is often the preferred approach for capturing RDS messages, applications using Arduino based on ATmega328 face limitations as they can only utilize two pins for interrupts (D2 and D2). These pins are typically allocated for encoder control, leaving no interrupt-capable pins available for FM/RDS application control. In such scenarios, resorting to the polling approach becomes necessary for retrieving RDS messages.

The code below shows the polling approach to get RDS messages.

```cpp

#include <SI4735.h>

#define RESET_PIN 16 // Arduino Nano / UNO pin A2

SI4735 rx;
void setup()
{
  rx.setup(RESET_PIN, FM_FUNCTION);
  rx.setFM(8400, 10800, currentFrequency, 10);
  delay(500);
  rx.setRdsConfig(3, 3, 3, 3, 3);
  rx.setFifoCount(1);
}

char *utcTime;
char *stationName;
char *programInfo;
char *stationInfo;

void showStationName() {
  if (stationName != NULL) {
    // do something
  }
}

void showStationInfo() {
  if (stationInfo != NULL) {
    // do something
  }
}

void showProgramaInfo() {
  if (programInfo != NULL) {
    // do something
  }
}

void showUtcTime() {
  if (rdsTime != NULL) {
    // do something
  }
}

void checkRds() {
 // The char pointer variables above will be populate by the call below. So, these variable (pointers) need to be passed by reference (pointer to pointer). 
 if (rx.getRdsAllData(&stationName, &stationInfo , &programInfo, &rdsTime) ) {
      showStationName(stationName); // you need check if stationName is null in showStationName
      showStationInfo(stationInfo); // you need check if stationInfo is null in showStationInfo
      showProgramaInfo(programInfo); // you need check if programInfo is null in showProgramaInfo
      showUtcTime(rdsTime); // you need check if rdsTime is null in showUtcTime
 }
}

void loop()
{
  .
  .
  .
  if (rx.isCurrentTuneFM()) {
    checkRds();
  }
  .
  .
  .
  delay(5);
}
```

### SI4735 Patch Support for Single Side Band

The SI4735 class implements a set of methods to apply patches and deal with SSB mode. All API documentation about patches can be seen [here](https://pu2clr.github.io/SI4735/extras/apidoc/html/group__group17.html).

The SSB patches used in some examples of this library were tested only on SI4735-D60 and SI4732-A10 devices.  __The updates used in those examples are unlikely to work on other SI47XX devices__.

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
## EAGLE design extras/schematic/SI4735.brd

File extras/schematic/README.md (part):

# [Schematics and Sketches](https://pu2clr.github.io/SI4735/extras/schematic/)

This section presents several prototypes and circuits with different displays and controller boards. The source codes for each prototype are stored in the [examples folder](https://github.com/pu2clr/SI4735/tree/master/examples) of this repository. Please, check the comments at the beginning of each sketch example available in this library. You will find the SI473X, button, encoder, display and Arduino settings. There are more than 30 projects that can help you to build your own receiver based on the SI47XX IC family.

__THE CIRCUIT DESIGNS CREATED BY THE AUTHOR ARE NOT INTEND TO BE A FINAL PRODUCT. SOME IMPORTANT ASPECTS OF A GOOD RECEIVER ARE OUTSIDE THE SCOPE OF THESE EXAMPLES. THE CIRCUITS MADE BY THE AUTHOR ARE A PROOF OF CONCEPT OF THE FUNCTIONS IMPLEMENTED IN THE ARDUINO LIBRARY. SO, COMPONENTS LIKE RF FRONT-END, BAND PASS FILTER, ESD, ANTENNA DESIGN ARE NOT THE MAIN PART OF THIS PROJECT__.

__This project is about a library to control the SI47XX devices and the focus of this project is the library and its functionalities. Please, don't ask the author to assist you with displays, encoders, buttons or something else outside of the "PU2CLR SI4735 Arduino Library" scope. Thanks.__

### Use the following groups to guide you in your projects

* __Facebook__ group called [__Si47XX for Radio Experimenters__](https://www.facebook.com/groups/532613604253401/). The purpose is exchanging experiences with projects based on Silicon Labs  SI47XX IC family.
* __group.io__ [SI47XX for hobbyists](https://groups.io/g/si47xx). This group is formed by people with experience in electronics and firmware development.

## Donate 

If you find this project useful, consider making a donation so that the author of this library can purchase components and modules for improvements and testing of this library. [Click here to donate](https://www.paypal.com/donate/?business=LLV4PHKTXC4JW&no_recurring=0&item_name=Consider+making+a+donation.+So%2C+I+can+purchase+components+and+modules+for+improvements+and+testing+of+this+library.&currency_code=USD) or use the QR code below.

## SI4735 and SI4732 pinout

If a schematic uses the SI4735 device but you have the SI4732 device or vice-versa, then reference the table below to correct the pinout for your specific IC model. See pictures and the table __SI4735-D60 and SI4732-A10 replacement__  below.

### The picture below shows the SI4735-D60/SI4730-D60 pinout (SSOP)

### The picture below shows the SI4732-A10 pinout (16L SOIC Package)

### SI4735-D60 and SI4732-A10 replacement

| SI4735-D60 PIN      | SI4732-A10 PIN     | Note |
| ------------------- | ------------------ | -----|
| #3 (GP03/[DCLK])    | #2 (GP03/[DCLK])   |      |
| #8 (FMI)            | #6 (FMI)           |      |
| #9 (RFGND)          | #7 (RFGND)         | Depending on your design, you can use this pin connected to GND |
| #10 and #11 (NC)    | Not applicable     | Connected to GND if you have the SI4735 |
| #12 (AMI)           | #8 (AMI)           |      |
| #13 and #14 (GND)   | #15 (GND)          |      |
| #15 (RST)           | #9 (RST)           |      |
| #16 (SEN)           | #10 (SENB)         | __(*1 ) See the text ATTENTION below__ |
| #17 (SCLK)          | #11 (SCLK)         |      |
| #18 (SDIO)          | #12 (SDIO)         |      |
| #19 (RCLK)          | #13 (RCLK)         |      |
| #20 and #21 (VD VA) | #14 (VDD)          | Connected to +VCC (between 2.8V and 3.7V) |
| #22 (DBYP)          | Not applicable     |      |
| #23 (ROUT/DOUT)     | #16 (ROUT/DOUT)    |      |
| #24 (LOUT/DFS)      | #1 (LOUT/DFS)      |      |

(*1) __ATTENTION__:

While the Si4735 device provides the 0x11 I²C bus address when the SEN pin is connected to ground, the SI4732-A10 provides the same address when the SENB pin is connected to +VCC. The SI4735 Arduino Library provides the function __getDeviceI2CAddress__ to detect the I²C bus address automatically. The library will detect and use the correct address if you use this function. See [getDeviceI2CAddress()](https://pu2clr.github.io/SI4735/extras/apidoc/html/group__group05.html#ga668008457910e916ebadf15bda2e5b29). By default, connect SEN/SENB pin to the GND. See schematics below.

<BR>

### Basic Schematic (Atmega328 based board)

The two schematics below show the basic setup. The first schematic uses the SI4735-D60 and the secound schematic uses the SI4732-A10. These schematics will help you to replace the SI4735-D60 with the SI4732-A10 or vice versa.

#### SI4735-D60 Version

The schematic below shows how to connect the SI473X (SSOP24 package) circuit with Arduino Pro Mini 3.3V/8MHz.

[All Sketches on SI47XX_01_SERIAL_MONITOR folder](https://github.com/pu2clr/SI4735/tree/master/examples/SI47XX_01_SERIAL_MONITOR)

|Part	| Description |
|-------| ------------ |
| C1    | 22nF Monolithic Multilayer Chip Ceramic non polarized capacitor (Place it close to VA pin)|
| C2    | 1nF Monolithic Multilayer Chip Ceramic non polarized capacitor |
| C3    | 470nF Monolithic Multilayer Chip Ceramic non polarized capacitor|
| C4    | 100nF Monolithic Multilayer Chip Ceramic non polarized capacitor (Place it close to VD pin)|
| C5 and C6 | 22pF (Crystal load capacitors) |
| C7 and C8 *1 | 4.7uF Monolithic Multilayer Chip Ceramic non polarized capacitor |
| R3    | 2.2K |
| (R4 and R5) *2 | 2.2K to 10K (pull-up resistors) |
| L1 | Ferrite loop stick (about 500 μH) |
| X1    | 32.768 kHz crystal |
| SI4735 | digital CMOS AM(LW, MW and SW)/FM radio receiver IC |

#### SI4732-A10 Version

The schematic below shows how to connect the SI4732-A10 circuit with Arduino Pro Mini 3.3V/8MHz.

[All Sketches on SI47XX_01_SERIAL_MONITOR folder](https://github.com/pu2clr/SI4735/tree/master/examples/SI47XX_01_SERIAL_MONITOR)

<BR>
<BR>

## Atmega328 based board and OLED

Sketche [SI47XX_02_ALL_IN_ONE_OLED](https://github.com/pu2clr/SI4735/blob/master/examples/SI47XX_03_OLED_I2C/SI47XX_02_ALL_IN_ONE_OLED/)

<BR>

## ESP32 based board

The schematic below guides you to build a SI473X based receiver using the ESP32 device.

#### ESP32 basic setup

#### ESP32 DEVKIT with OLED and Encoder setup

[All Sketches on SI47XX_06_ESP32 folder](https://github.com/pu2clr/SI4735/tree/master/examples/SI47XX_01_SERIAL_MONITOR)

* [Si4735 Arduino Library - Arduino Mega 2560 and ESP32 LOLIN32 WEMOS](https://youtu.be/HrxR-bUqbjw)

{% include esp32_mega2560.html %}

## ESP8266

### ESP8266 basic schematic

### ESP8266 OLED

#### ESP8266-12-F with OLED

#### Generic ESP8266 with OLED

[All Seeeduino sketches on /examples/SI47XX_06_ESP8266 folder](https://github.com/pu2clr/SI4735/tree/master/examples/SI47XX_06_ESP8266)

## Seeeduino XIAO

[Youtube](https://youtu.be/hua0JLIlTeA)

[All Seeeduino sketches on examples/SI47XX_15_SEEEDUINOX_06_ESP32 folder](https://github.com/pu2clr/SI4735/tree/master/examples/SI47XX_15_SEEEDUINO)

<BR>

## Standalone ATmega328 with or without external Crystal (SI4735-D60 and LCD 16x2). 

The schematic below can be also used with a regular Arduino Board based on ATmega328. It is almost the same circuit posted by Mirko Pavleski on his [Arduino Project repository](https://create.arduino.cc/projecthub/mircemk/diy-si4730-all-band-radio-lw-mw-sw-fm-1894d9). If you use an SI4735-D60 or SI4732-A10, you can have an All band receiver with FM, AM and SSB modes. 

Sketch [SI47XX_02_for_Mirko_Pavleski_radio](https://github.com/pu2clr/SI4735/tree/master/examples/SI47XX_02_for_Mirko_Pavleski_radio).

Please, use the [MiniCore](https://github.com/MCUdude/MiniCore) setup on your Arduino IDE to deal with standalone Atmega328.

See  video:

* [All band receiver based on SI473X and standalone ATmega328 Modes: FM (VHF) and AM and SSB (HF)](https://youtu.be/H-uIJclH9l8)

{% include atmega328_standalone.html %}

<BR>

## Basic schematic with TFT

The schematic below demonstrates how to build your own receiver based on the SI473X with TFT display. The sketches are available on [examples/SI47XX_04_TFT/](https://github.com/pu2clr/SI4735/tree/master/examples/SI47XX_04_TFT) folder decribe the wire up used by the TFT selected by the author. Please, read the comments at the beginning of each sketch example.

Sketches on [examples/SI47XX_04_TFT/](https://github.com/pu2clr/SI4735/tree/master/examples/SI47XX_04_TFT)

See video:
[Si4735 All in One Receiver running on Arduino Pro Mini 3.3V (8MHz) and TFT Display](https://youtu.be/oL8qyRglZ8I)

{% include videoSSB.html %}

<BR>

## Arduino DUE/MEGA and touch TFT display.

The schematic below shows just the Arduino DUE and SI473X connections. The touch TFT used by this circuit is a shield that can be connected to the Arduino DUE directly. If you intent to use Arduino Mega, you have to add a bidirectional logic level converter. 

Sketches on [SI47XX_10_RDS](https://github.com/pu2clr/SI4735/tree/master/examples/SI47XX_10_RDS)

See videos:

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
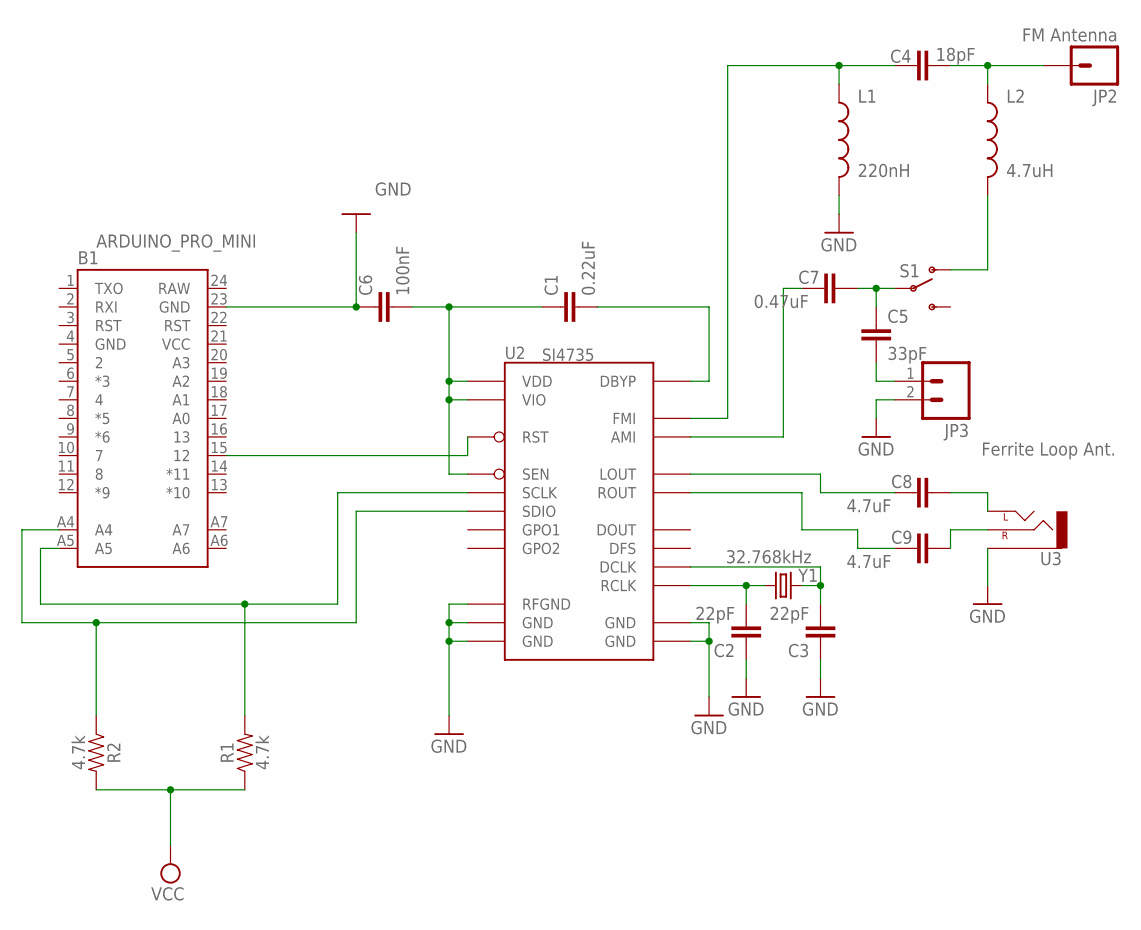
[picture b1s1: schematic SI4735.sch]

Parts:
B1: ARDUINO_PRO_MINI
C1: 0.22uF; 0402-CAP
C2, C3: 22pF; 0402-CAP
C4: 18pF; 0402-CAP
C5: 33pF; 0402-CAP
C6: 100nF; 0402-CAP
C7: 0.47uF; 0402-CAP
C8, C9: 4.7uF; 0402-CAP
JP2: FM Antenna; 1X01
JP3: Ferrite Loop Ant.; 1X02
L1: 220nH; C0402
L2: 4.7uH; C0402
R1, R2: 4.7k; 0603
S1: SWITCH-SPSTSMD; AYZ0202
U2: SI4735; SSOP24_NARROW
U3: AUDIO-JACKSMD2; AUDIO-JACK-3.5MM-SMD
Y1: 32.768kHz; CRYSTAL-32kHz-SMD

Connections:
GND: B1.4 (GND), B1.23 (GND), C2.1, C3.1, C6.1, JP3.2, L1.2, U2.9 (RFGND), U2.10 (GND), U2.11 (GND), U2.13 (GND), U2.14 (GND), U3.SLEEVE
unnamed: C2.2, U2.19 (RCLK), Y1.X1 (1)
unnamed: C3.2, U2.3 (DCLK), Y1.X2 (2)
unnamed: B1.15 (12), U2.15 (RST)
unnamed: C1.2, U2.22 (DBYP)
unnamed: B1.A5, R1.2, U2.17 (SCLK)
unnamed: B1.A4, R2.1, U2.18 (SDIO)
unnamed: C4.1, L1.1, U2.8 (FMI)
unnamed: C4.2, JP2.1, L2.1
unnamed: L2.2, S1.1 (O)
unnamed: C5.1, C7.1, S1.2
unnamed: C7.2, U2.12 (AMI)
unnamed: C5.2, JP3.1
unnamed: C9.1, U3.RING (RIGHT)
unnamed: C8.1, U3.TIP (LEFT)
unnamed: C8.2, U2.24 (LOUT)
unnamed: C9.2, U2.23 (ROUT)
RAD_PWR: C1.1, C6.2, U2.16 (SEN), U2.20 (VIO), U2.21 (VDD)
RAW: B1.24 (RAW)
VCC: B1.21 (VCC), R1.1, R2.2

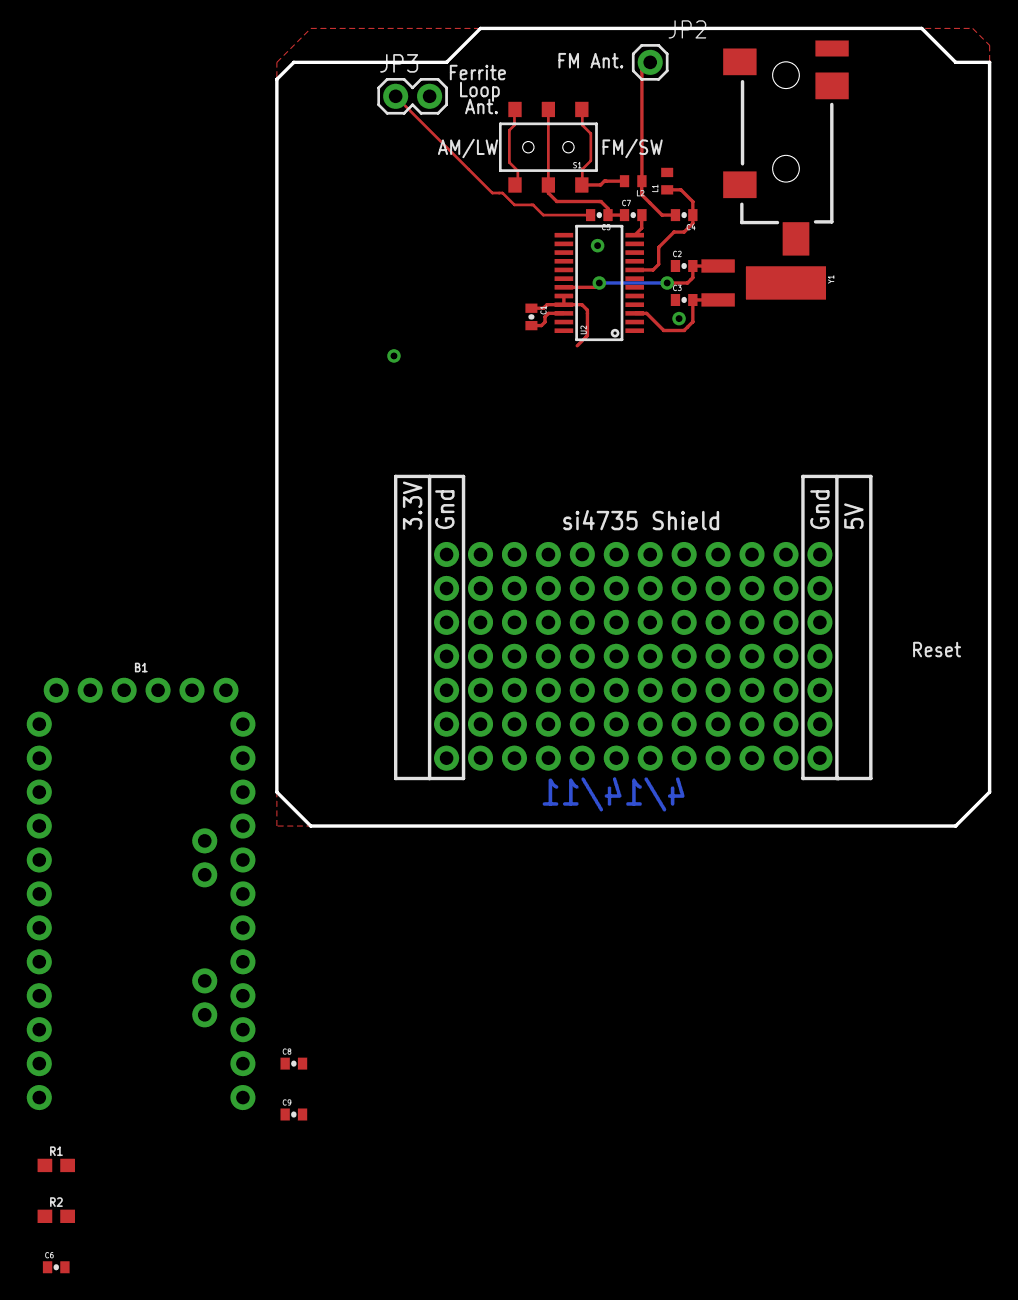
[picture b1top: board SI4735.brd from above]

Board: 2 copper layers, 53.3 x 59.7 mm, 20 parts (0 on the bottom side), 19 nets.

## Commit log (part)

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2023-01-17 Examples
2023-01-20 Documentation
2023-01-23 SI473X Arduino Library
2023-02-15 Update README.md
    Documentation
2023-02-16 Update README.md
    Examples
2023-02-20 Exmples
2023-02-21 Exambples
2023-02-27 Reworded some documentation to enhance readability. Fixed typos.
2023-02-27 Fixed typos that I missed.
2023-02-27 Basic rewording to make documentation easier to read.
2023-02-27 Cleaned up README.md
2023-02-27 Things I missed on my first pass
2023-02-27 Extras
2023-02-28 Documentation
    Documentation
    Documentation
    Cleanup one documentation file
2023-03-10 Example documentation
    Make txt into md
    Writing manuals in markdown
2023-03-16 SI4735 Arduino LIbrary
2023-03-20 Delete .vscode directory
    SI473X
2023-04-17 SI573X Arduino Library
2023-05-11 RDA5807 Arduino Library
2023-06-22 API Documentation
2023-07-20 User guides
2023-07-30 Documentation/Donation
2023-07-30 Documentation / Donate
2023-09-11 Example
2023-10-27 Spelling and grammar of documentation and comments
2024-05-11 Typo fixes, some paragraph rewritten for grammar reasons. No changes to the actualy source code, documentation only.
2025-06-10 Teste
2025-06-10 Fix variable name typo
2025-06-10 Add simple ESP32C3 example using serial monitor
2025-06-10 Fix documentation typos and comments
2025-06-10 Doc Codex
2025-06-29 Update SI4735.cpp
    搜索bug
2026-04-28 Revise donation message for clarity and detail
    Updated the donation section to clarify the purpose and conditions of donations.

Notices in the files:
parts and their libraries:
SparkFun-Boards: Licensing: Creative Commons ShareAlike 4.0 International - https://creativecommons.org/licenses/by-sa/4.0
